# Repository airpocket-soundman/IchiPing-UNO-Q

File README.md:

# UNO Ping

**One speaker, one microphone, every window and door.** UNO Ping plays a 2-second noise "ping" into a home and classifies which of five windows and doors are open from the way the rooms filter that sound. This repository is the **Arduino UNO Q** port: real-time I/O on the STM32U585, audio and a 1D CNN on the Qualcomm QRB2210 Linux side, all in one Arduino App Lab app.

- Contest article (Hackster, Home Automation): [docs/hackster/story_en.md](docs/hackster/story_en.md) — Japanese review copy: [docs/hackster/story_ja.md](docs/hackster/story_ja.md)
- Documentation site (GitHub Pages): https://airpocket-soundman.github.io/IchiPing-UNO-Q/

## Results at a glance

Held-out UNO Q evaluation sets, 32-state / 14-class (observable) accuracy:

| Evaluation set | Condition | 32-state | 14-class |
|---|---|---|---|
| 09:00 | stable | 91.7 % | 100 % |
| 19:35 | temperature drift (−2.15 % frequency warp) | 81.9 % | 100 % |
| 20:44 | drift −1.05 % | 74.7 % | 100 % |
| 21:28 | crowd noise playing | 81.9 % | 100 % |

The original FRDM-MCXN947 model scored 20.8 % on the same hardware; real UNO Q sessions, cross-baseline training, ambient noise and a new temperature (frequency-warp) augmentation took it to 82.5 % mean, while the observable classes stay at 100 %.

## Documentation

| Page | Contents |
|---|---|
| [Hardware and wiring](docs/uno_q/hardware.md) | BOM, MCU pins, 1.8 V MI2S0 audio wiring, safety rules |
| [Software architecture](docs/uno_q/software.md) | App Lab app, Bridge services, audio worker, TFT rendering |
| [Acoustic sensing and model](docs/uno_q/signal_and_model.md) | PRBS excitation, features, model, observability |
| [Data collection and training](docs/uno_q/data_and_training.md) | automated collection, sessions, training recipe, temperature augmentation |
| [Results](docs/uno_q/results.md) | accuracy on held-out sets, beyond the observable region, resources |
| [Reproduce](docs/uno_q/reproduce.md) | step-by-step build, deploy and training guide |
| [Model comparison](pc/runs/model_comparison_20260912.md) | all 23 trained models with their augmentation |
| [Shield PCB design](hardware/easyeda/IchiPing-UNO-Q-Shields/SPECIFICATION.md) | EasyEDA audio and TFT shields, BOMs, pin maps |

## Repository layout

| Path | Contents |
|---|---|
| `uno_q/app/` | Arduino App Lab app: `sketch/` (STM32U585), `python/` (Linux runtime), `models/` (deployed ONNX + manifest) |
| `uno_q/audio/` | MI2S0 Device Tree overlay, ALSA route and safe capture tools, audio worker, offline tests |
| `pc/uno_q_*.py` | data collection, dataset export, evaluation and comparison tools |
| `pc/training/` | dataset loader, augmentation (incl. `--freq-warp`), training script |
| `docs/uno_q/` | documentation (Markdown sources; HTML is generated by `tools/build_site.py`) |
| `hardware/easyeda/`, `board/` | UNO Q shield PCB design (EasyEDA Pro; latest project `board/Ichiping uno q.eprj2`). Designed by an AI assistant as an experiment: the schematics are not very readable, but the circuits are correct and the boards work. |
| `hardware/3d_parts/` | STL files for the 3D-printed model house |
| `hardware/bom.*`, `docs/pins.xlsx` | shield BOM and the original pin sheet referenced by the shield specification |
| `pc/captures/full_32_eval_v1/` | small original-dataset fixture used by `test_packaged_model.py` |

The FRDM-MCXN947 firmware, its documents and datasets live in the original project: https://github.com/airpocket-soundman/IchiPing.

## Tests

```bash
python -m unittest discover -s uno_q/app/python -p "test_*.py"
python -m unittest discover -s uno_q/audio -p "test_*.py"
```

## License

Inherits the license conditions of the original IchiPing project. Code derived from Arduino examples follows the license of each file.

---

日本語の概要：1つのスピーカーと1つのマイクで、住まいの5か所の窓・扉の開閉を音で推定するプロジェクト UNO Ping です（IchiPing の Arduino UNO Q 移植版）。記事の日本語確認版は [docs/hackster/story_ja.md](docs/hackster/story_ja.md) にあります。

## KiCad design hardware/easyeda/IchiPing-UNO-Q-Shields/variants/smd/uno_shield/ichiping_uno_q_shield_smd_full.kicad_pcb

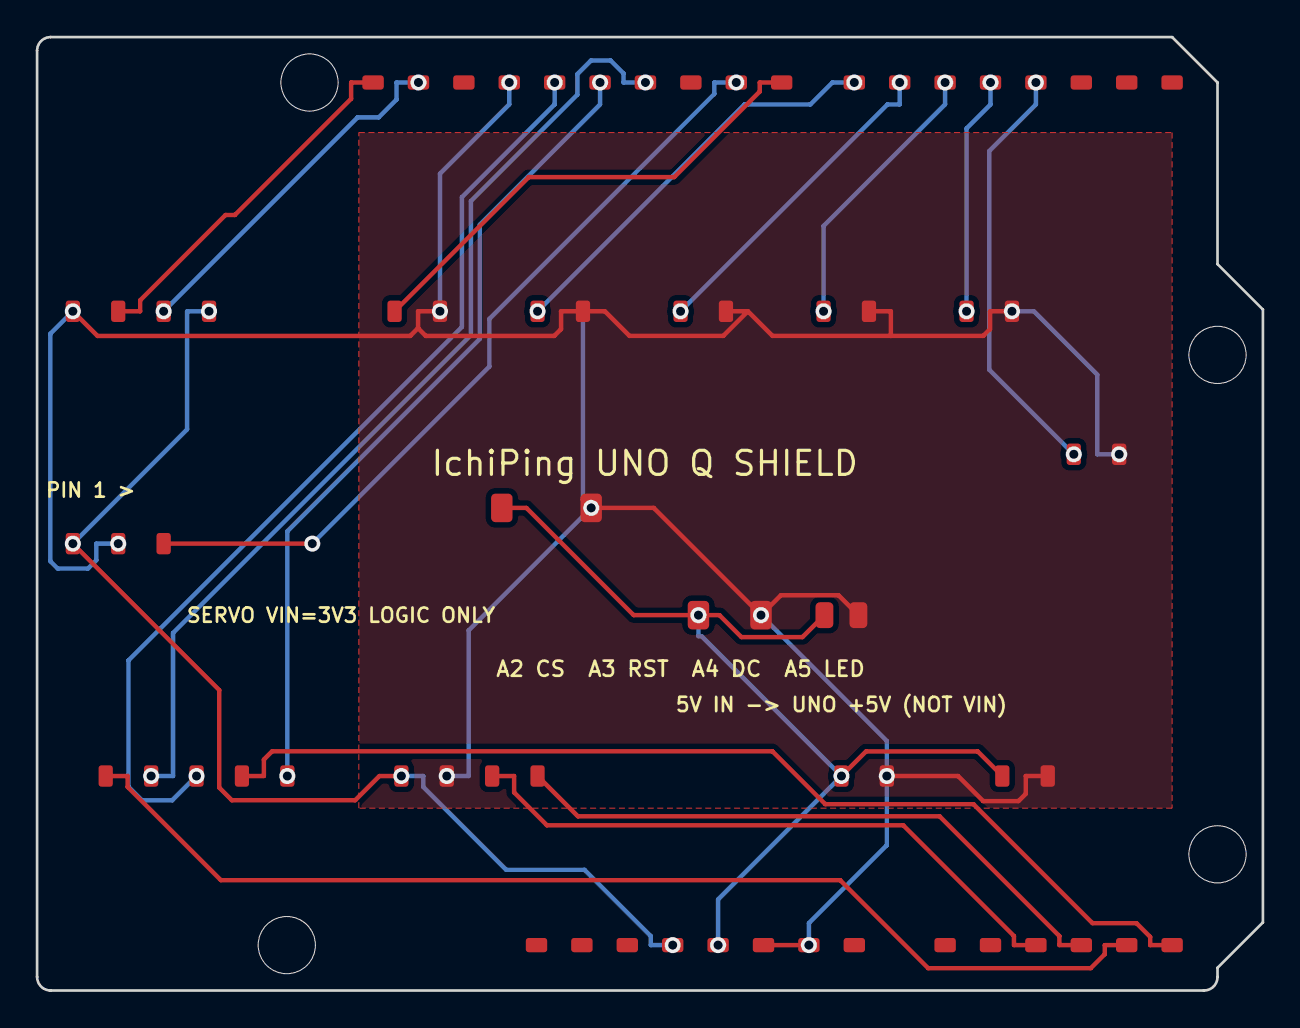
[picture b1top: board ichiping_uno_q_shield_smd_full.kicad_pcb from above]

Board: 2 copper layers, 68.6 x 53.3 mm, 23 parts (0 on the bottom side), 19 nets.

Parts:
C_PWR_BULK: 470u 10V LOW ESR
C_PWR_HF: 100n
C_SERVO_BULK: 1000u LOW ESR
J1: Power
J2, J4: Digital/PWM
J3: Analog
J_DOOR_AB: XH2.54_Vertical_1x02:D6_DOOR_AB/GND
J_DOOR_BC: XH2.54_Vertical_1x02:D7_DOOR_BC/GND
J_EXEC: XH2.54_Vertical_1x02:D8_EXEC/GND
J_PWR_IN: XH2.54_Vertical_1x02:+5V/GND
J_RAIN: XH2.54_Vertical_1x03:+3V3/GND/D9_RAIN
J_SERVO_5V_OUT: XH2.54_Vertical_1x02:+5V/GND
J_SERVO_CTRL: XH2.54_Vertical_1x04:GND/D21_SCL/D20_SDA/+3V3
J_TFT_PWR: XH2.54_Vertical_1x04:A3/A2/GND/+3V3
J_TFT_SIG: XH2.54_Vertical_1x05:D12_MISO/A5/D13_SCK/D11_MOSI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
J_WIN_A: XH2.54_Vertical_1x02:D3_WIN_A/GND
J_WIN_B: XH2.54_Vertical_1x02:D4_WIN_B/GND
J_WIN_C: XH2.54_Vertical_1x02:D5_WIN_C/GND
MH1, MH2, MH3, MH4: UNO mounting hole

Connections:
+3V3: J1.4, J_RAIN.1, J_SERVO_CTRL.4, J_TFT_PWR.4
+5V: C_PWR_BULK.1, C_PWR_HF.1, C_SERVO_BULK.1, J1.5, J_PWR_IN.1, J_SERVO_5V_OUT.1
A2: J3.3, J_TFT_PWR.2
A3: J3.4, J_TFT_PWR.1
A4: J3.5, J_TFT_SIG.5
A5: J3.6, J_TFT_SIG.2
D3_WIN_A: J4.5, J_WIN_A.1
D4_WIN_B: J4.4, J_WIN_B.1
D5_WIN_C: J4.3, J_WIN_C.1
D6_DOOR_AB: J4.2, J_DOOR_AB.1
D7_DOOR_BC: J4.1, J_DOOR_BC.1
D8_EXEC: J2.10, J_EXEC.1
D9_RAIN: J2.9, J_RAIN.3
D11_MOSI: J2.7, J_TFT_SIG.4
D12_MISO: J2.6, J_TFT_SIG.1
D13_SCK: J2.5, J_TFT_SIG.3
D20_SDA: J2.2, J_SERVO_CTRL.3
D21_SCL: J2.1, J_SERVO_CTRL.2
GND: C_PWR_BULK.2, C_PWR_HF.2, C_SERVO_BULK.2, J1.6, J1.7, J2.4, J_DOOR_AB.2, J_DOOR_BC.2, J_EXEC.2, J_PWR_IN.2, J_RAIN.2, J_SERVO_5V_OUT.2, J_SERVO_CTRL.1, J_TFT_PWR.3, J_WIN_A.2, J_WIN_B.2, J_WIN_C.2

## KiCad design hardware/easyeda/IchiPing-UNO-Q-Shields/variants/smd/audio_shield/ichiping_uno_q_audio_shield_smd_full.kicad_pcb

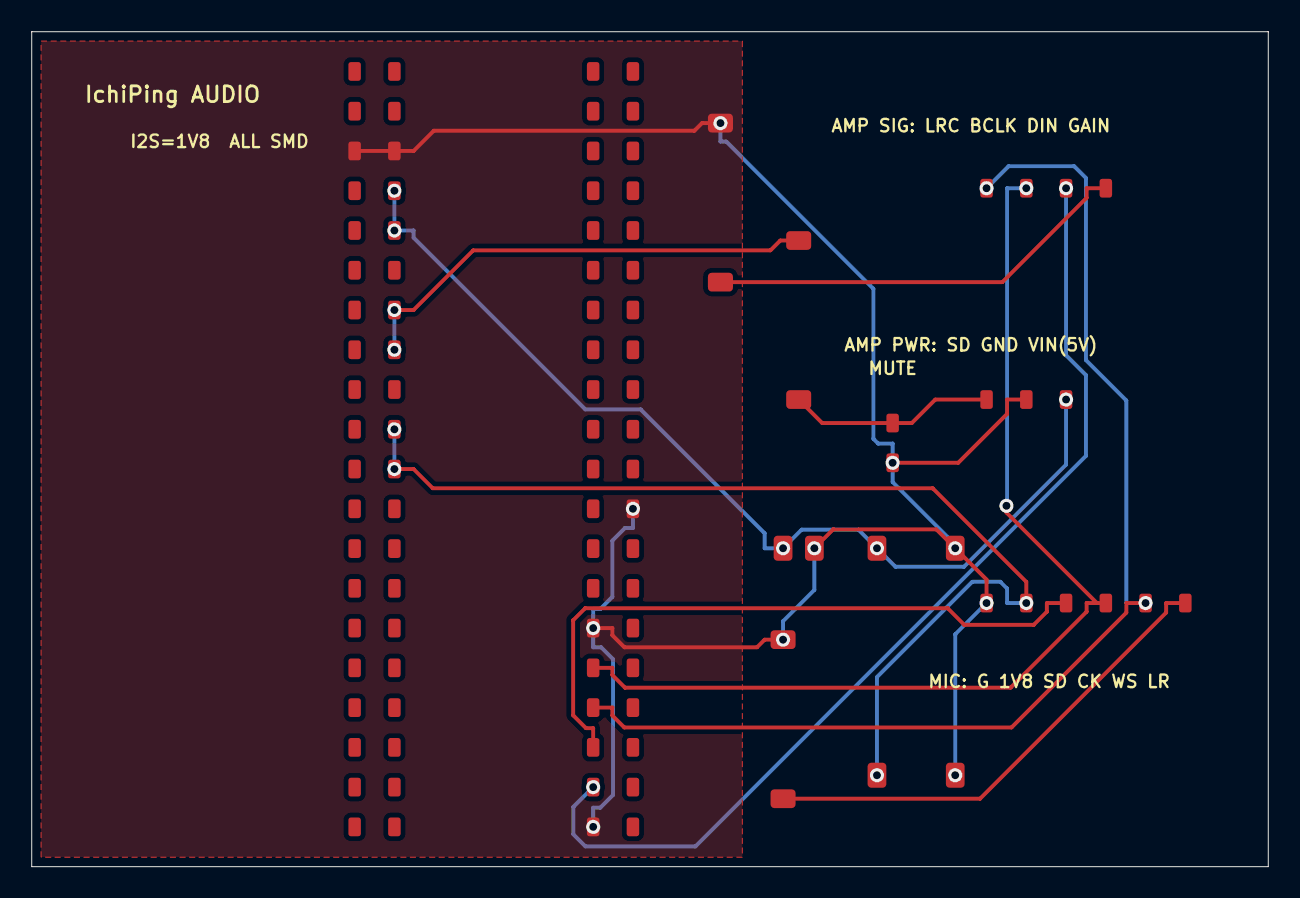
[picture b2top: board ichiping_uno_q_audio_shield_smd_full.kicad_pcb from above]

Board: 2 copper layers, 79.0 x 53.3 mm, 12 parts (0 on the bottom side), 11 nets.

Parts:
C1: 10u 10V
C2, C3: 100n
J14: UNO Breakout Carrier J14
J15: UNO Breakout Carrier J15
JP_MUTE: AMP SD MUTE (OPEN)
J_AMP_PWR: XH2.54_Vertical_1x03:AMP_SD/GND/+5V
J_AMP_SIG: XH2.54_Vertical_1x04:MI2S0_WS/MI2S0_CLK/MI2S0_DAT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
J_MIC: XH2.54_Vertical_1x06:GND/+1V8/MI2S0_DATA0/MI2S0_C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
R_GAIN: 0R GAIN=GND
R_LR: 0R MIC_LR=GND
R_SD: 100k SD pull-up

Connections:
+1V8: C3.1, J14.19, J14.21, J_MIC.2
+3V3: J14.13, J14.15, R_SD.2
+5V: C1.1, C2.1, J14.7, J14.9, J_AMP_PWR.3
AMP_GAIN: J_AMP_SIG.4, R_GAIN.1
AMP_SD: JP_MUTE.1, J_AMP_PWR.1, R_SD.1
GND: C1.2, C2.2, C3.2, J14.5, J14.6, J15.23, J15.30, J15.40, JP_MUTE.2, J_AMP_PWR.2, J_MIC.1, R_GAIN.2, R_LR.2
MI2S0_CLK: J15.32, J_AMP_SIG.2, J_MIC.4
MI2S0_DATA0: J15.36, J_MIC.3
MI2S0_DATA1: J15.38, J_AMP_SIG.3
MI2S0_WS: J15.34, J_AMP_SIG.1, J_MIC.5
MIC_LR: J_MIC.6, R_LR.1
